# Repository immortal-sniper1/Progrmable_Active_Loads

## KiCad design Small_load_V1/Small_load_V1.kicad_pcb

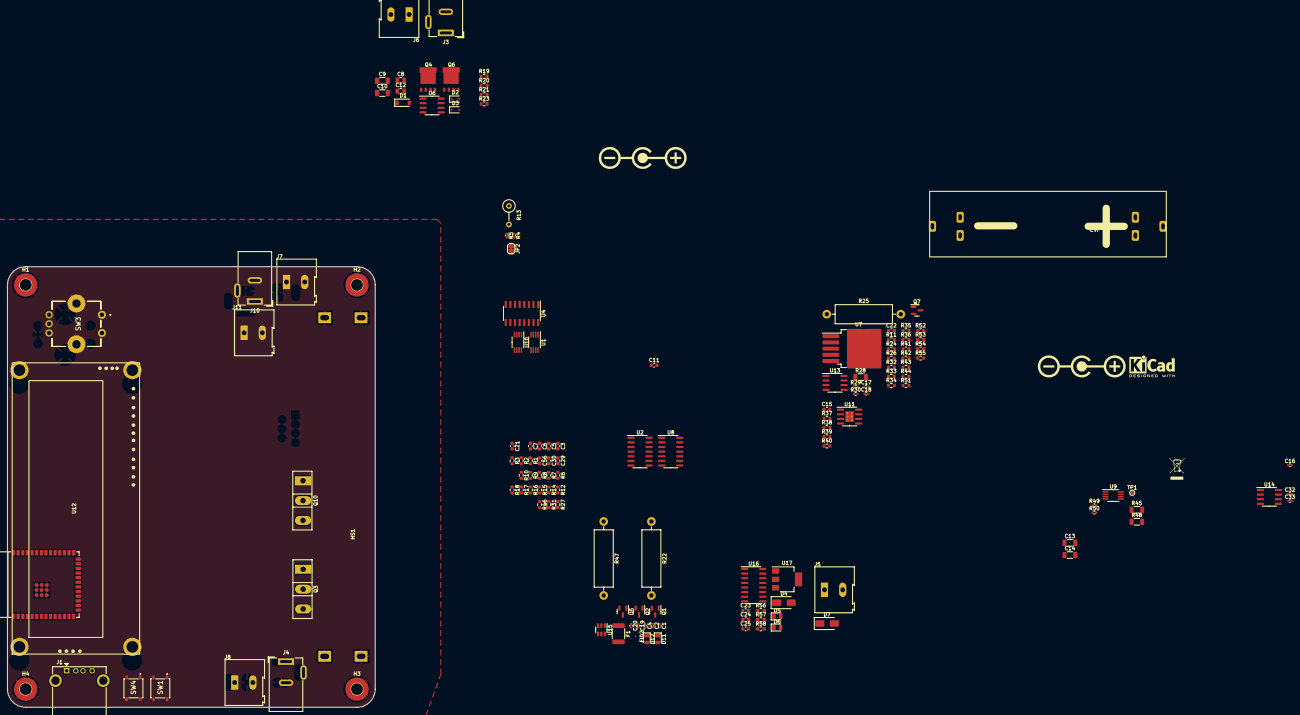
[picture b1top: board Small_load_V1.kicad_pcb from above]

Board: 2 copper layers, 101.0 x 121.0 mm, 147 parts (0 on the bottom side), 81 nets, no tracks yet.

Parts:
C1, C2, C4, C16, C18, C19, C20, C33: 1u; C_0402_1005Metric
C3, C22, C56: 100p; C_0603_1608Metric
C5, C6, C7, C11, C15, C21, C23: 100n; C_0603_1608Metric
C8: 10u@50V; C_0805_2012Metric
C9, C10, C13, C14: 10u; C_1206_3216Metric
C12: 10u; C_0805_2012Metric
C17, C32: 4n7; C_0402_1005Metric
C24, C25, C29, C30: 10u; C_0603_1608Metric
D1: B5819W_SL; D_SOD-123
D2, D3: 1N5819WS; D_SOD-323
D4, D7: SS54; D_SMA
D5, D6: LED_Small; LED_0805_2012Metric
D11, D12: green; LED_0805_2012Metric
F1: Polyfuse; R_1812_4532Metric_Pad1.30x3.40mm_HandSolder
FID1: kicad; KiCad-Logo2_5mm_SilkScreen
FID2: Fiducial; Fiducial_0.5mm_Mask1.5mm
FID3: trash; WEEE-Logo_4.2x6mm_SilkScreen
FID4, FID7: Polarity; Polarity_Center_Positive_6mm_SilkScreen
H1, H2, H3, H4: M3; MountingHole_3.2mm_M3_Pad_TopBottom
HS1: Heatsink; heatsink1
J1: USB_B; USB_A_CONNFLY_DS1095-WNR0
J3, J4, J10: Jack-DC; BarrelJack_Wuerth_6941xx301002
J5, J6, J7, J11: Input; TerminalBlock_Altech_AK300-2_P5.00mm
J8: INPUT; TerminalBlock_Altech_AK300-2_P5.00mm
J12: Conn_01x02; MYOUNG MY-18650-01
JP2: Jumper_2_Bridged; SolderJumper-2_P1.3mm_Bridged_RoundedPad1.0x1.5mm
Q1, Q2, Q7: 2N7002; SOT-23
Q3, Q10: IRFZ24NPBF; TO-247-3_Vertical
Q4, Q6: HYG025N06LS1C2; DFN-8_(5x6)
R1, R7: 3k; R_0603_1608Metric
R2, R6, R8, R10, R11, R12, R33, R39, R40: 1k; R_0603_1608Metric
R3, R9, R14, R16, R17, R18, R24, R31, R34, R35, R36, R37, R41, R42, R43, R46, R53, R55: 10k; R_0603_1608Metric
R4: 470; R_0402_1005Metric
R5: 2k; R_0402_1005Metric
R13: 1k; R_Axial_DIN0309_L9.0mm_D3.2mm_P5.08mm_Vertical
R15, R26, R27: 100; R_0603_1608Metric
R19, R20, R21, R23, R54: 56; R_0603_1608Metric
R22: 1; R_Axial_DIN0516_L15.5mm_D5.0mm_P20.32mm_Horizontal
R25, R47: 50m; R_Axial_DIN0516_L15.5mm_D5.0mm_P20.32mm_Horizontal
R28, R45, R48: 0R1; R_1206_3216Metric
R29, R30, R49, R50: 5R1; R_0402_1005Metric
R32: 16k; R_0603_1608Metric
R38: 24k; R_0603_1608Metric
R44: 2.7M; R_0603_1608Metric
R51: 330k; R_0603_1608Metric
R52: 1M; R_0603_1608Metric
R56, R57, R58: 300; R_0603_1608Metric_Pad0.98x0.95mm_HandSolder
SW1, SW4: SW_SPST; PTS526SK15SMTR2LFS
SW3: RotaryEncoder_Switch; PEC12R4230FS0024
TP1: TestPoint; TestPoint_Pad_D1.0mm
U1, U9, U10: AD5337; MSOP-8_3x3mm_P0.65mm
U2, U8: LM324; SOIC-14_3.9x8.7mm_P1.27mm
U3: ESP32-S3-WROOM-1
U4: MCP3208; SOIC-16_3.9x9.9mm_P1.27mm
U5: CJ431; SOT-23
U6: LM5109BMA; SOIC-8_3.9x4.9mm_P1.27mm
U7: LT3080xQ; TO-263-5_TabPin3
U11: TPS5430DDAR; SOIC-8-1EP_3.9x4.9mm_P1.27mm_EP2.29x3mm_ThermalVias
U12: 1602_LCD_I2C; 1602_LCD_mine
U13, U14: INA219AxD; SOIC-8_3.9x4.9mm_P1.27mm
U15: SRV05-4; SOT-23-6
U16: CH340C; SOIC-16_3.9x9.9mm_P1.27mm
U17: AMS1117-3.3; SOT-223-3_TabPin2

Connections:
+3V3: C1.2, C4.2, C16.2, C18.2, C19.2, C20.2, C25.1, C29.1, C30.1, C33.2, D5.2 (A), D6.2 (A), D12.2 (A), Q1.1 (G), Q2.1 (G), R3.2, R4.2, R5.1, R9.2, R13.2, R17.2, R18.2, R34.2, R35.2, R36.2, R41.2, R53.2, SW3.S1, U1.1 (VDD), U3.2 (3V3), U4.16 (Vdd), U9.1 (VDD), U10.1 (VDD), U10.8 (A0), U13.5 (VS), U14.5 (VS), U17.2 (VO)
+5V: C21.1, C24.1, D11.2 (A), F1.1, R14.2, R16.2, U8.4 (V+), U16.16 (VCC), U17.3 (VI)
+15V: C8.2, D1.2 (A), U6.1 (VDD)
/BOOT: C6.1, R3.1, SW4.2 (B), U3.27 (GPIO0/BOOT)
/BUCK_EN: R37.2, U11.5 (ENA)
/CELL_CHARGER/Buck_out: R38.2, R45.1, R48.1, R49.1
/CELL_CHARGER/DAC1: TP1.1, U9.2 (Vout_A)
/CELL_CHARGER/DAC2: R40.1, U9.3 (Vout_B)
/DAC1: U1.2 (Vout_A), U8.3 (+)
/DAC2: U1.3 (Vout_B), U8.5 (+)
/DAC3: U2.10 (+), U10.2 (Vout_A)
/DAC4: U2.12 (+), U10.3 (Vout_B)
/EN: C7.1, R9.1, SW1.2 (B), U3.3 (EN)
/LDO_Vcc: C11.1, C22.1, D4.1 (K), J10.1, J11.2, R46.2, U2.4 (V+)
/LDO_Vin: R55.2, U2.6 (-), U2.7
/LDO_Vout: J7.2, R28.1, R30.1
/Load_current_main: R42.2, U8.13 (-), U8.14
/Load_voltage: R43.2, U8.8, U8.9 (-)
/SW_OUT: R31.2, SW3.S2
/buck/HB1: C12.1, D1.1 (K), U6.8 (HB)
/buck/HO1: R19.1, R20.2, U6.7 (HO)
/buck/LO1: R21.1, R23.2, U6.5 (LO)
/buck/gate_H1: D2.2 (A), Q4.3 (G), R20.1
/buck/gate_L1: D3.2 (A), Q6.3 (G), R21.2
D+: J1.3 (D+), U15.1 (IO1), U16.5 (UD+)
D-: J1.2 (D-), U15.6 (IO4), U16.6 (UD-)
GND: C1.1, C2.1, C4.1, C5.2, C6.2, C7.2, C8.1, C9.2, C10.2, C11.2, C13.2, C14.2, C16.1, C18.1, C19.1, C20.1, C21.2, C23.2, C24.2, C25.2, C29.2, C30.2, C33.1, D7.2 (A), H1.1, H2.1, H3.1, H4.1, HS1.1, HS1.2, J1.4 (GND), J3.2, J4.2, J5.1, J6.1, J7.1, J8.2, J10.2, J11.1, J12.2, JP2.1 (A), Q6.2 (S), Q7.2 (S), R1.1, R7.1, R11.2, R12.2, R22.2, R31.1, R33.2, R37.1, R39.1, R42.1, R43.1, R47.2, R52.1, R55.1, SW1.1 (A), SW3.C, SW3.MH (MH1), SW4.1 (A), U1.5 (GND), U1.8 (A0), U2.3 (+), U2.11 (V-), U3.1 (GND), U3.40 (GND), U3.41 (GND), U4.9 (DGND), U4.14 (AGND), U5.3 (A), U6.4 (VSS), U8.11 (V-), U9.5 (GND), U9.8 (A0), U10.5 (GND), U11.6 (GND), U11.9 (Thermal), U13.1 (A1), U13.2 (A0), U13.6 (GND), U14.1 (A1), U14.2 (A0), U14.6 (GND), U15.2 (VN), U16.1 (GND), U17.1 (GND)
I2C_CLK: Q2.3 (D), R16.1
I2C_CLK_3V3: Q2.2 (S), R18.1
I2C_SDA: Q1.3 (D), R14.1
I2C_SDA_3V3: Q1.2 (S), R17.1
LOAD: J4.1, J8.1, Q3.2 (D), Q10.2 (D), R44.2
unnamed: C3.1, R27.2, U8.1
unnamed: C56.1, R15.2, U8.7
unnamed: D2.1 (K), R19.2
unnamed: D3.1 (K), R23.1
unnamed: D4.2 (A), R28.2, R29.1, U7.3 (OUT)
unnamed: D5.1 (K), R57.2
unnamed: D6.1 (K), R58.2
unnamed: C15.2, D7.1 (K), U11.8 (PH)
unnamed: D11.1 (K), R8.1
unnamed: D12.1 (K), R10.1
unnamed: J5.2, U11.7 (Vin)
unnamed: C13.1, C14.1, J6.2
unnamed: J12.1, R45.2, R48.2, R50.1
unnamed: JP2.2 (B), R8.2, R10.2
unnamed: Q3.1 (G), R27.1
unnamed: Q3.3 (S), R6.1, R47.1, U8.12 (+)
unnamed: C9.1, C10.1, J3.1, Q4.1 (D)
unnamed: C12.2, Q4.2 (S), Q6.1 (D), U6.6 (HS)
unnamed: C22.2, R26.1
unnamed: Q7.3 (D), R51.1
unnamed: Q7.1 (G), R53.1, R54.1
unnamed: Q10.1 (G), R15.1
unnamed: Q10.3 (S), R2.1, R22.1
unnamed: R26.2, U2.14
unnamed: U2.1, U2.2 (-)
unnamed: R12.1, R46.1, U2.5 (+)
unnamed: R11.1, R24.1, U2.9 (-)
unnamed: R32.1, R33.1, U2.13 (-)
unnamed: R25.2, R32.2, U7.4 (VCONTROL), U7.5 (IN)
unnamed: R24.2, U2.8, U7.2 (SET)
unnamed: C3.2, R1.2, R6.2, U8.2 (-)
unnamed: C56.2, R2.2, R7.2, U8.6 (-)
unnamed: R44.1, R51.2, R52.2, U8.10 (+)
unnamed: C15.1, U11.1 (BOOT)
unnamed: R38.1, R39.2, R40.2, U11.4 (VSENSE)
unnamed: C17.1, R29.2, U13.8 (IN+)
unnamed: C17.2, R30.2, U13.7 (IN-)
unnamed: C32.1, R49.2, U14.8 (IN+)
unnamed: C32.2, R50.2, U14.7 (IN-)
unnamed: R56.2, U16.3 (RXD)
unnamed: C23.1, U16.4 (V3)
REF_2v5: C2.2, C5.1, R4.1, R5.2, U1.4 (REF), U4.15 (Vref), U5.1 (REF), U5.2 (K), U9.4 (REF), U10.4 (REF)
SCL: R41.1, U1.7 (SCL), U10.7 (SCL), U13.4 (SCL)
SCL1: R35.1, U9.7 (SCL), U14.4 (SCL)
SDA: R36.1, U1.6 (SDA), U10.6 (SDA), U13.3 (SDA)
SDA1: R34.1, U9.6 (SDA), U14.3 (SDA)
UART0_RX: R57.1, U3.37 (U0TXD/GPIO43/CLK_OUT1), U16.2 (TXD)
UART0_TX: R56.1, R58.1, U3.36 (U0RXD/GPIO44/CLK_OUT2)
VBUS: F1.2, J1.1 (VBUS), U15.5 (VP)
